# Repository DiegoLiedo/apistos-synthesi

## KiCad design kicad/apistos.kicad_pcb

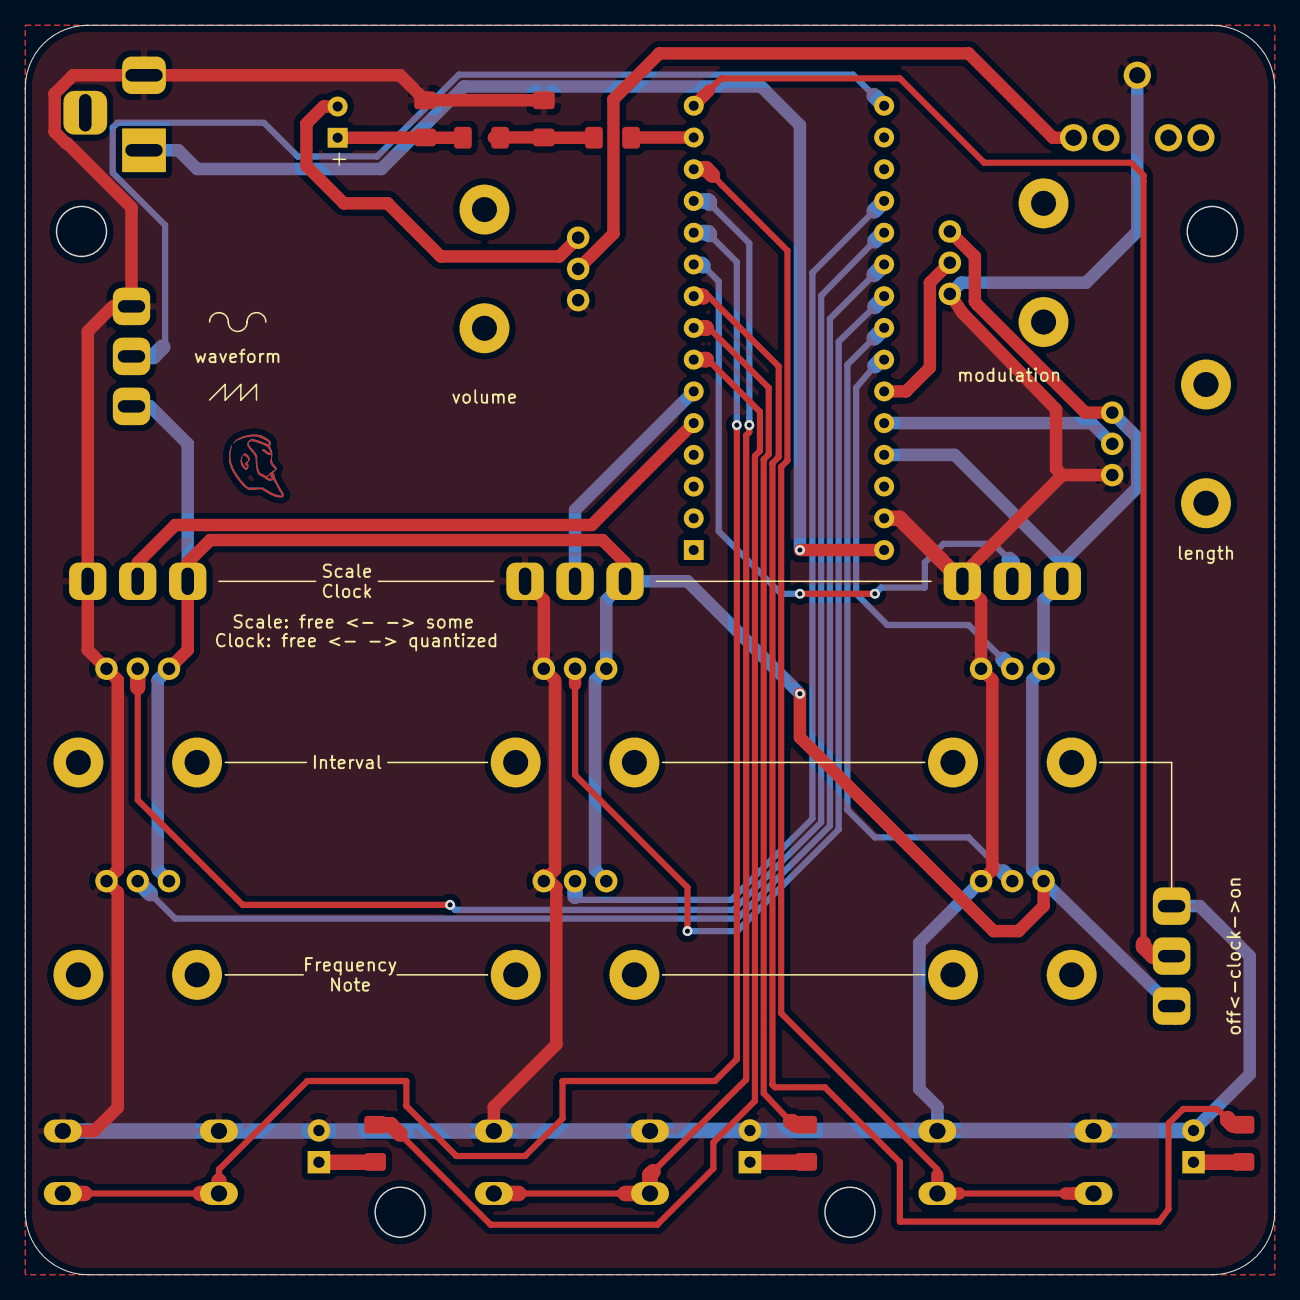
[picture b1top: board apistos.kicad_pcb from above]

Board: 2 copper layers, 100.0 x 100.0 mm, 31 parts (1 on the bottom side), 30 nets.

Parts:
A1: Arduino_Nano_v3.x; Arduino_Nano
C1: 10µF; CP_Radial_D10.0mm_P2.50mm
C2: 473; C_1206_3216Metric_Pad1.42x1.75mm_HandSolder
C3: 104; C_1206_3216Metric_Pad1.42x1.75mm_HandSolder
D1, D2, D3: LED; LED_D5.0mm
J1: AudioJack3_SwitchTR; AUDIO-JACK
J2: Barrel_Jack_Switch; BarrelJack_Horizontal
R1, R2, R3, R5: 1K; R_1206_3216Metric_Pad1.42x1.75mm_HandSolder
R4: 470K; R_1206_3216Metric_Pad1.42x1.75mm_HandSolder
RV1: freq1; Potentiometer_Alps_RK09L_Single_Vertical
RV2: int1; Potentiometer_Alps_RK09L_Single_Vertical
RV3: freq2; Potentiometer_Alps_RK09L_Single_Vertical
RV4: int2; Potentiometer_Alps_RK09L_Single_Vertical
RV5: frec3; Potentiometer_Alps_RK09L_Single_Vertical
RV6: int3; Potentiometer_Alps_RK09L_Single_Vertical
RV7: modulation; Potentiometer_Alps_RK09L_Single_Vertical
RV8: length; Potentiometer_Alps_RK09L_Single_Vertical
SW1, SW2, SW3: SW_SPDT_MSM; cola de rata
SW4: off<-clock->on; cola de rata
SW5: trigger1; SW_PUSH-12mm
SW6: trigger2; SW_PUSH-12mm
SW7: trigger3; SW_PUSH-12mm
SW8: waveform; cola de rata
volume1: volume; Potentiometer_Alps_RK09L_Single_Vertical

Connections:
+12V: A1.30, J2.1
AudioOUT: A1.14, R4.1
GND: A1.29, C2.2, C3.2, D1.2, D2.2, D3.2, J1.S, J2.2, RV1.1, RV2.1, RV3.1, RV4.1, RV5.1, RV6.1, RV7.1, RV8.1, SW1.3, SW2.3, SW3.3, SW4.3, SW5.2, SW6.2, SW7.2, SW8.3, volume1.3
unnamed: A1.19, RV1.2
unnamed: A1.20, RV2.2
unnamed: A1.21, RV3.2
unnamed: A1.22, RV4.2
unnamed: A1.23, RV5.2
unnamed: A1.24, RV6.2
unnamed: A1.25, RV7.2
unnamed: A1.26, RV8.2
unnamed: C1.1, C3.1, R5.2
unnamed: C1.2, volume1.1
unnamed: C2.1, R4.2, R5.1
unnamed: D1.1, R1.2
unnamed: D2.1, R2.2
unnamed: D3.1, R3.2
unnamed: J1.T, volume1.2
VCC: A1.27, RV1.3, RV2.3, RV3.3, RV4.3, RV5.3, RV6.3, RV7.3, RV8.3, SW1.1, SW2.1, SW3.1, SW4.1, SW8.1
clock: A1.15, SW4.2
led1: A1.7, R1.1
led2: A1.8, R2.1
led3: A1.9, R3.1
scale1: A1.5, SW1.2
scale2: A1.6, SW2.2
scale3: A1.10, SW3.2
trigger1: A1.11, SW5.1
trigger2: A1.12, SW6.1
trigger3: A1.13, SW7.1
waveform: A1.16, SW8.2

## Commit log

2020-09-11 Create readme.txt
    Kicad files for pcb production
2020-09-11 Create s
2020-09-11 correction to file names
    correction to file names
2020-09-25 firmware improvements
    v.1.2 adds a "reverse envelope"
    while initiating apistos, if a trigger button is pressed the envelope of that voice reverses.
    v.1.2_arthur_henry_s_fork was commisioned for custom "note scales"
